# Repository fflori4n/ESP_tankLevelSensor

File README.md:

# ESP_tankLevelSensor

ESP32 measuring water level in a reservoar, using an external LM555 oscillator and a capacitive probe. 

Measurements are displayed on MAX7219 driven 7seg. displays and the uController hosts it's on webserver that displays the tank status and stats. Board has a linear regulator to drop the 12V DC from the truck's battery to 5V for the ESP and the sensor, two relays that can switch 12V DC external loads ( meant for signal lights ), and can drive WS2812B LED strip to indicate level in the tank.

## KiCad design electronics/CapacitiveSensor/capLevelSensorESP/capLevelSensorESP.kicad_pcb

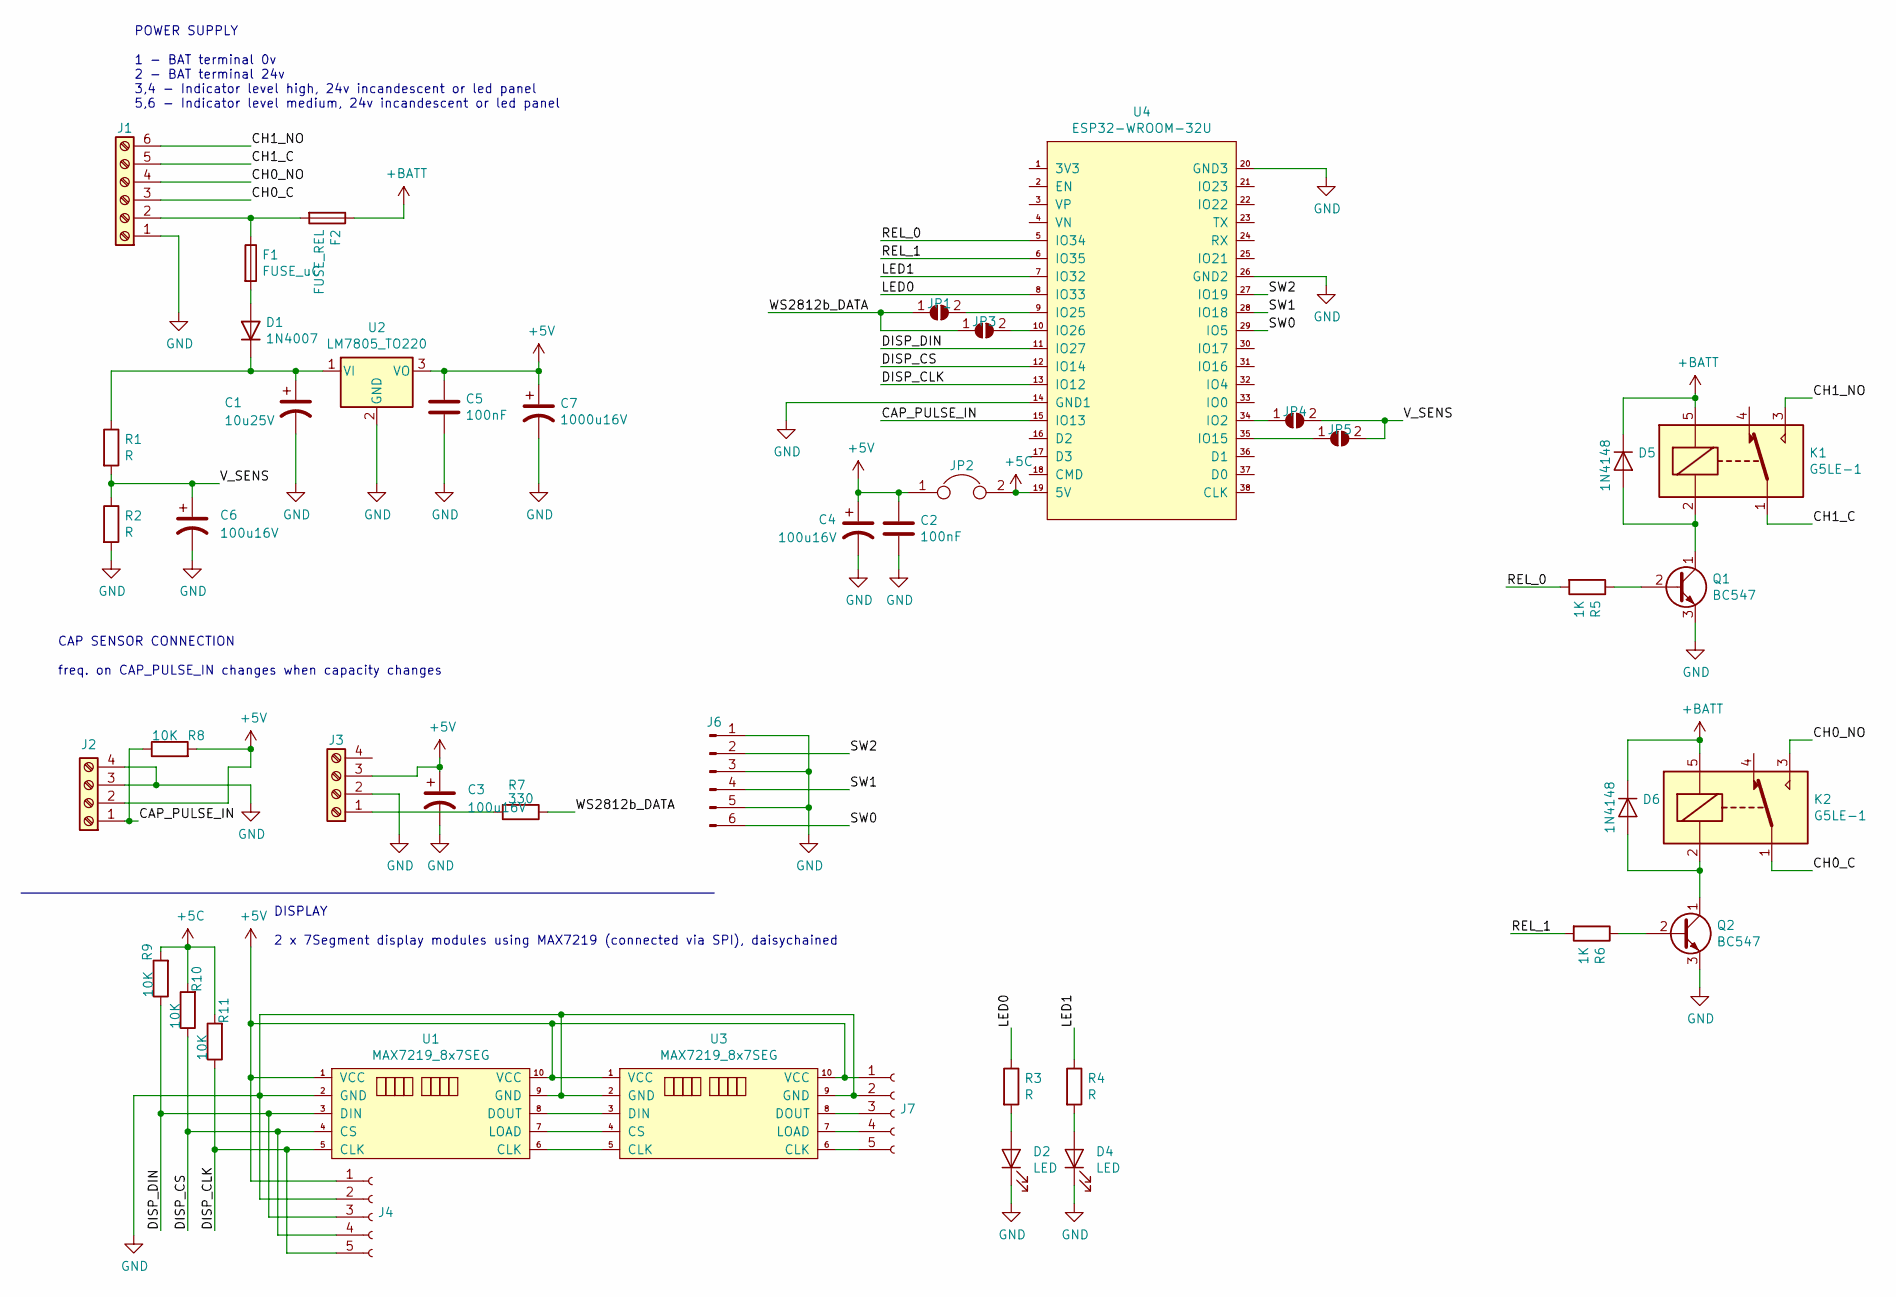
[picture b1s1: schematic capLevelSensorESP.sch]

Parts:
C1: 10u25V; CP_Radial_D6.3mm_P2.50mm
C2, C5: 100nF; Capker_L4.6mm_W2.0mm_P2.50mm
C3, C4, C6: 100u16V; CP_Radial_D6.3mm_P2.50mm
C7: 1000u16V; CP_Radial_D10.0mm_P5.00mm_P7.50mm
D1: 1N4007; D_DO-41_SOD81_P10.16mm_Horizontal
D2, D4: LED; LED_D5.0mm_FlatTop
D5, D6: 1N4148; D_DO-35_SOD27_P7.62mm_Horizontal
F1: FUSE_uC; resistor0.25,9mm
F2: FUSE_REL; resistor0.25,9mm
J1: TerminalBlock_bornier-6_P5.08mm
J2, J3: TerminalBlock_bornier-4_P5.08mm
J4, J7: PinHeader_1x05_P2.54mm_Vertical
J6: PinHeader_1x06_P2.54mm_Vertical
JP1, JP3, JP4, JP5: SolderJumper-2_P1.3mm_Open_Pad1.0x1.5mm
JP2: PinHeader_1x02_P2.54mm_Vertical
K1, K2: G5LE-1; Relay_SPDT_Omron-G5LE-1
Q1, Q2: BC547; TO-92_Inline
R1, R2, R3, R4: R; resistor0.25,9mm
R5, R6: 1K; resistor0.25,9mm
R7: 330; resistor0.25,9mm
R8, R9, R10, R11: 10K; resistor0.25,9mm
U1, U3: MAX7219_8x7SEG; 7SEG_DISPX8_MAX7219
U2: LM7805_TO220; TO-220-3_Horizontal_TabDown
U4: ESP32-WROOM-32U

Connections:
+5C: JP2.2, R9.2, R10.2, R11.2, U4.19 (5V); also elsewhere on the board
+5V: C2.1, C3.1, C4.1, C5.1, C7.1, J2.2, J3.3, J4.1, J7.1, JP2.1, R8.2, U1.1 (VCC), U1.10 (VCC), U2.3 (VO), U3.1 (VCC), U3.10 (VCC); also elsewhere on the board
+BATT: D5.1 (K), D6.1 (K), F2.1, K1.5, K2.5
/CAP_PULSE_IN: J2.1, R8.1, U4.15 (IO13); also elsewhere on the board
/CH0_C: J1.3, K2.1
/CH0_NO: J1.4, K2.3
/CH1_C: J1.5, K1.1
/CH1_NO: J1.6, K1.3
/DISP_CLK: J4.5, R11.1, U1.5 (CLK), U4.13 (IO12); also elsewhere on the board
/DISP_CS: J4.4, R10.1, U1.4 (CS), U4.12 (IO14); also elsewhere on the board
/DISP_DIN: J4.3, R9.1, U1.3 (DIN), U4.11 (IO27); also elsewhere on the board
/LED0: R3.1, U4.8 (IO33); also elsewhere on the board
/LED1: R4.1, U4.7 (IO32); also elsewhere on the board
/REL_0: R5.2, U4.5 (IO34); also elsewhere on the board
/REL_1: R6.2, U4.6 (IO35); also elsewhere on the board
/SW0: J6.6, U4.29 (IO5); also elsewhere on the board
/SW1: J6.4, U4.28 (IO18); also elsewhere on the board
/SW2: J6.2, U4.27 (IO19); also elsewhere on the board
/V_SENS: C6.1, JP4.2 (B), JP5.2 (B), R1.2, R2.1
/WS2812b_DATA: JP1.1 (A), JP3.1 (A), R7.1
GND: C1.2, C2.2, C3.2, C4.2, C5.2, C6.2, C7.2, D2.1 (K), D4.1 (K), J1.1, J2.3, J2.4, J3.2, J4.2, J6.1, J6.3, J6.5, J7.2, Q1.3 (E), Q2.3 (E), R2.2, U1.2 (GND), U1.9 (GND), U2.2 (GND), U3.2 (GND), U3.9 (GND), U4.14 (GND1), U4.20 (GND3), U4.26 (GND2); also elsewhere on the board
unnamed 21: C1.1, D1.2 (K), R1.1, U2.1 (VI); also elsewhere on the board
unnamed: D1.1 (A), F1.2
unnamed: D2.2 (A), R3.2
unnamed: D4.2 (A), R4.2
unnamed: D5.2 (A), K1.2, Q1.1 (C)
unnamed: D6.2 (A), K2.2, Q2.1 (C)
unnamed: F1.1, F2.2, J1.2
unnamed: J3.1, R7.2
unnamed: J7.3, U3.8 (DOUT)
unnamed: J7.4, U3.7 (LOAD)
unnamed: J7.5, U3.6 (CLK)
unnamed 33: JP1.2 (B), U4.9 (IO25); also elsewhere on the board
unnamed 34: JP3.2 (B), U4.10 (IO26); also elsewhere on the board
unnamed 35: JP4.1 (A), U4.34 (IO2); also elsewhere on the board
unnamed 36: JP5.1 (A), U4.35 (IO15); also elsewhere on the board
unnamed: Q1.2 (B), R5.1
unnamed: Q2.2 (B), R6.1
unnamed: U1.6 (CLK), U3.5 (CLK)
unnamed: U1.7 (LOAD), U3.4 (CS)
unnamed: U1.8 (DOUT), U3.3 (DIN)

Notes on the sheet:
POWER SUPPLY 1 - BAT terminal 0v 2 - BAT terminal 24v 3,4 - Indicator level high, 24v incandescent or led panel 5,6 - Indicator level medium, 24v incandescent or led panel
DISPLAY 2 x 7Segment display modules using MAX7219 (connected via SPI), daisychained
CAP SENSOR CONNECTION freq. on CAP_PULSE_IN changes when capacity changes

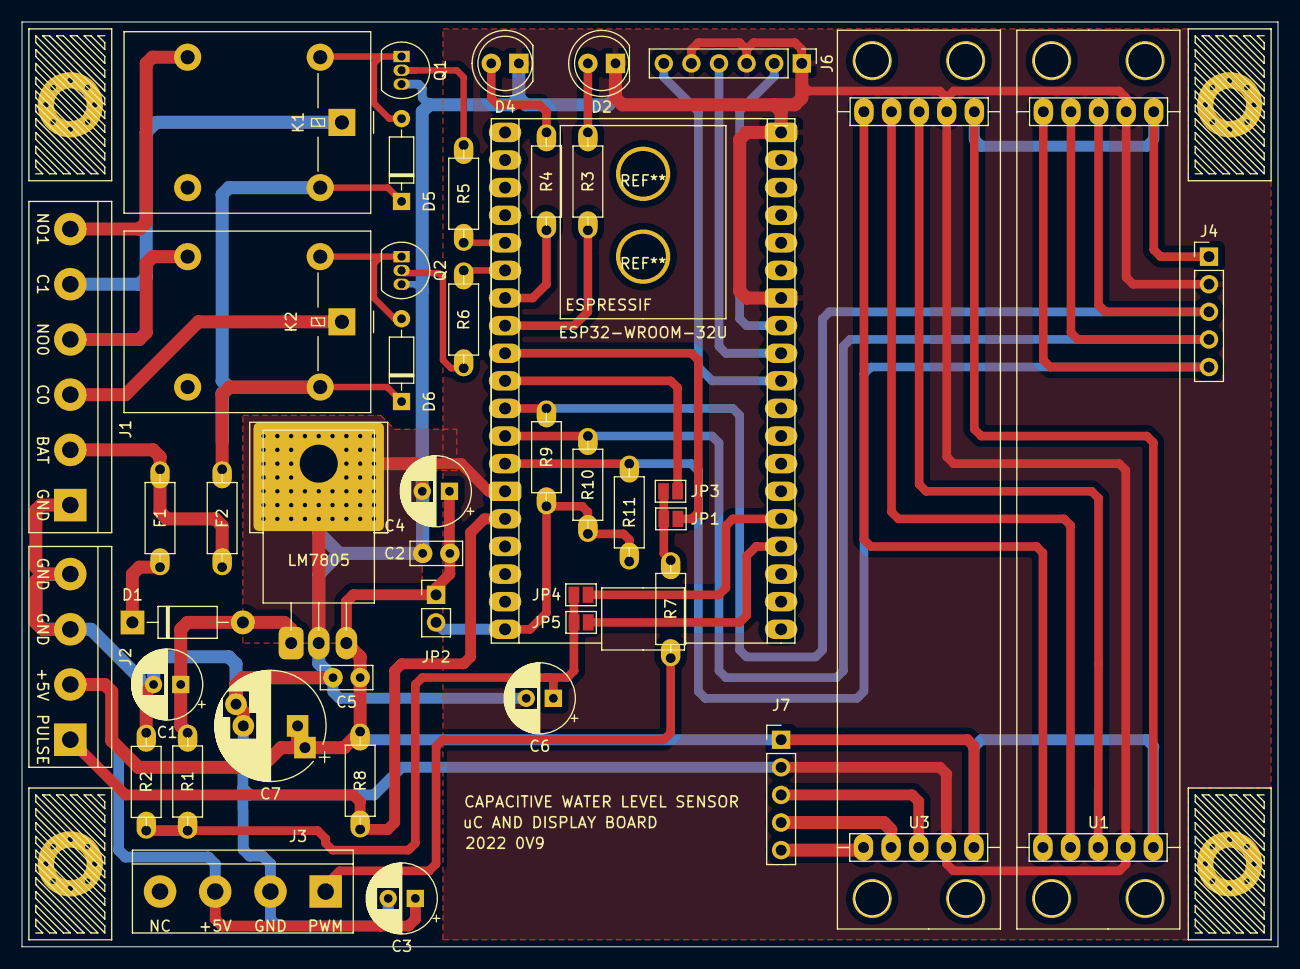
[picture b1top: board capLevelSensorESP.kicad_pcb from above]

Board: 2 copper layers, 115.6 x 85.1 mm, 48 parts (0 on the bottom side), 41 nets.

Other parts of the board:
 : MountingHole_3mm_Pad_Via
 #2,  #3,  #4: MountingHole_3mm_Pad_Via
 #5: ESP32-WROOM-32U
LM7805: LM7805_TO220; TO-220-3_Horizontal_TabDown

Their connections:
+5C: #5.19; also elsewhere on the board
+5V: LM7805.3; also elsewhere on the board
/CAP_PULSE_IN: #5.15; also elsewhere on the board
/DISP_CLK: #5.13; also elsewhere on the board
/DISP_CS: #5.12; also elsewhere on the board
/DISP_DIN: #5.11; also elsewhere on the board
/LED0: #5.8; also elsewhere on the board
/LED1: #5.7; also elsewhere on the board
/REL_0: #5.5; also elsewhere on the board
/REL_1: #5.6; also elsewhere on the board
/SW0: #5.29; also elsewhere on the board
/SW1: #5.28; also elsewhere on the board
/SW2: #5.27; also elsewhere on the board
GND: #5.14, #5.20, #5.26, LM7805.2; also elsewhere on the board
unnamed 21: LM7805.1; also elsewhere on the board
unnamed 33: #5.9; also elsewhere on the board
unnamed 34: #5.10; also elsewhere on the board
unnamed 35: #5.34; also elsewhere on the board
unnamed 36: #5.35; also elsewhere on the board

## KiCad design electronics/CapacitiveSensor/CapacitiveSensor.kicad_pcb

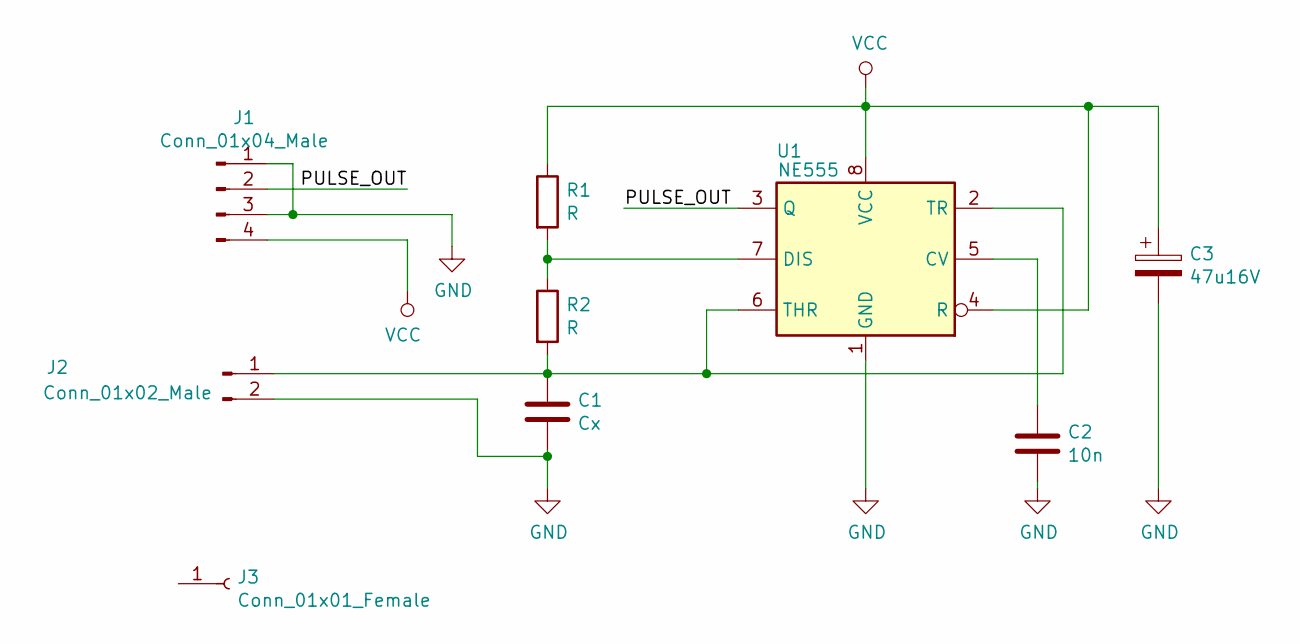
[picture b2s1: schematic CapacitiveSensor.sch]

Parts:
C1: Cx; Capker_L4.6mm_W2.0mm_P2.50mm
C2: 10n; Capker_L4.6mm_W2.0mm_P2.50mm
C3: 47u16V; CP_Radial_D7.5mm_P2.50mm
J1: Conn_01x04_Male; CopperPad_4x4_withZipTie
J2: Conn_01x02_Male; CopperPad_2x0.75
J3: Conn_01x01_Female; 4mmcableSteainRelief
R1, R2: R; resistor0.25,9mm
U1: NE555; DIP-8_W7.62mm_Large

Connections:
/PULSE_OUT: J1.2, U1.3 (Q)
GND: C1.2, C2.2, C3.2, J1.1, J1.3, J2.2, U1.1 (GND)
unnamed: C1.1, J2.1, R2.2, U1.2 (TR), U1.6 (THR)
unnamed: C2.1, U1.5 (CV)
unnamed: R1.2, R2.1, U1.7 (DIS)
VCC: C3.1, J1.4, R1.1, U1.4 (R), U1.8 (VCC)

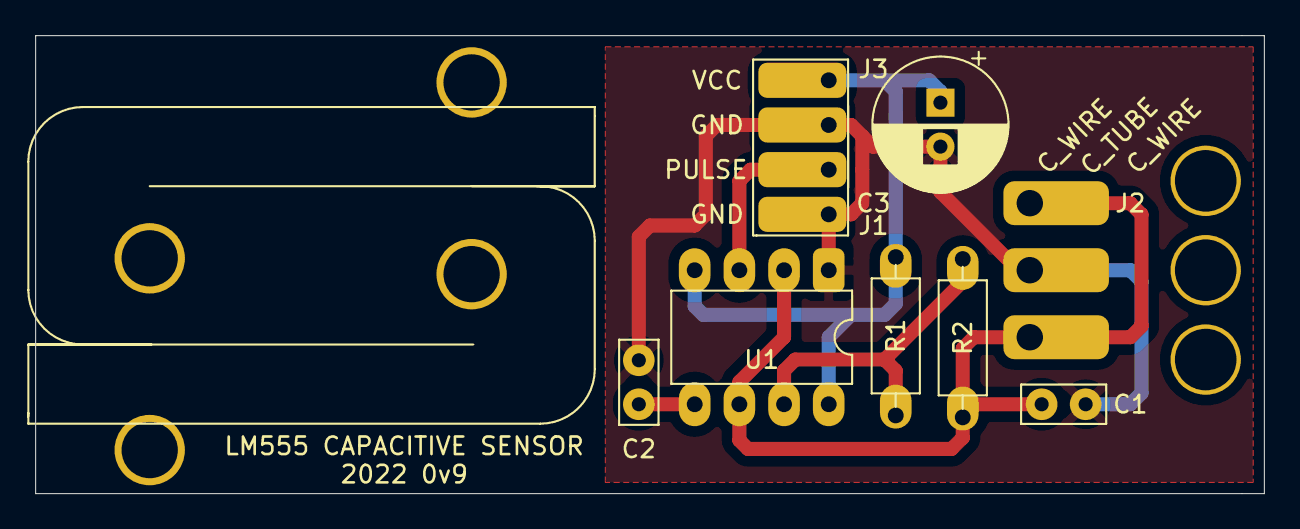
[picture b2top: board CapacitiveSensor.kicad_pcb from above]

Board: 2 copper layers, 69.8 x 26.0 mm, 9 parts (0 on the bottom side), 6 nets.

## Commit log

2022-08-09 Add files via upload
    First commit!
2022-11-21 Add files via upload
    needs some more work on web interface
2022-11-21 Update README.md
    description added
2022-11-21 Add files via upload
    schemes
2023-02-18 added calibration function
2023-02-19 probe calibrated, but TODO: optimise LUT process and add features to change calibration
2023-02-26 started writing proper display library for the MAX7219 8x8 displays
2023-02-26 new LUT function, display function and new 7seg display letters and symbols
2023-02-26 added kicad files for PCBs
2023-03-09 worked on web interface with my new best collegue, chatGPT. And updated values for 1040mm sensor instead of 1000mm
2023-03-09 worked on encoder and button actions, cleaned up main, added webpages (chatgpt does not know how water looks like XD, but whatever saved it for future reference it still helped me a lot)
2023-03-10 working on liquid level class, cleaning up stuff
2023-03-11 reworked the EEProm reading and writing
2023-03-12 managed to DeSpaghetify liquidLevel, and max7219.h display functions
2023-03-12 Wifi, added tags to webpage, worked on time until tank empty or full
2023-03-13 fixed bad pravopis && gramar
2023-03-15 fixed remaining time displayed format
2023-03-23 added minimum battery level, new probe will be calibrated again @TODO: add calc sheet to git
2023-03-23 added user wi-fi on off toggle and min bat that works
2023-06-10 Create LICENSE
